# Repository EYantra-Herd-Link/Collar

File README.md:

# HerdLink Collar V1

HerdLink Collar V1 is a smart edge-computing tracking and health monitoring collar designed for livestock. Built around the Seeed Studio XIAO ESP32-C3, the collar integrates motion sensing, temperature and humidity monitoring, and audio analysis to infer animal behaviors such as grazing, ruminating, walking, and resting. It transmits telemetry data wirelessly via UDP.

## Features

*   **Behavioral Inference:** Utilizes a 6-axis IMU (MPU6050) to calculate activity jerk and variance, categorizing behavior into states like Grazing, Ruminating, Walking, Resting, and High/Low Activity Alerts.
*   **Audio Edge Processing:** Captures audio via an I2S microphone and performs on-device Fast Fourier Transform (FFT) to extract Mel-frequency features and audio magnitude.
*   **Health & Environmental Monitoring:** Measures body temperature using a Dallas DS18B20 sensor and environmental temperature/humidity using an AHT20 sensor.
*   **Power Efficiency:** Implements FreeRTOS tasks, hardware interrupts, and sleep modes (ESP32 Light Sleep) to optimize battery life.
*   **Wireless Telemetry:** Broadcasts structured JSON telemetry payloads over WiFi via UDP for local network collection.

## Hardware Components

*   **Microcontroller:** Seeed Studio XIAO ESP32-C3
*   **Motion Sensor:** MPU6050 (Accelerometer & Gyroscope)
*   **Body Temperature Sensor:** Dallas DS18B20 (OneWire)
*   **Environment Sensor:** AHT20 (Temperature & Humidity)
*   **Microphone:** I2S Microphone
*   **Custom PCB:** KiCad designs included for the main logic board and power management board.

## Project Structure

*   `Board Firmware/Sender/`: C++ PlatformIO project containing the ESP32-C3 edge firmware.
*   `Board Firmware/Reciever/`: Python script to receive and decode UDP telemetry data.
*   `PCB_Design/HerdLinkV1/`: KiCad project and Gerber files for the main collar PCB.
*   `PCB_Design/HerdLinkV1 Power/PowerBoard/`: KiCad project for the power management board.

## Setup and Installation

### 1. Firmware (Sender)

The firmware is built using PlatformIO.

1.  Open the `Board Firmware/Sender` directory in VS Code with the PlatformIO extension installed.
2.  Before flashing, update the WiFi credentials in `src/main.cpp`:
    ```cpp
    const char* WIFI_SSID     = "Your_SSID";
    const char* WIFI_PASSWORD = "Your_PASSWORD";
    ```
3.  Connect the XIAO ESP32-C3 and click the PlatformIO "Upload" button to compile and flash the firmware.

### 2. Receiver (Python script)

The receiver is a lightweight Python script that listens for incoming UDP packets.

1.  Navigate to the receiver directory:
    ```bash
    cd "Board Firmware/Reciever"
    ```
2.  Run the script (requires Python 3):
    ```bash
    python CowPilled.py
    ```
    The script will bind to `0.0.0.0:4210` and print incoming JSON telemetry payloads to the console.

## Telemetry Data Format

The device transmits data in JSON format over UDP. Example payload structure:

```json
{
  "id": "MAC_ADDRESS",
  "seq": 123,
  "ts": 1645000,
  "bt": 38.5,
  "et": 24.2,
  "eh": 45.0,
  "ax": 0.05,
  "ay": 0.98,
  "az": 0.12,
  "gx": 1.50,
  "gy": -0.20,
  "gz": 0.10,
  "gy_var": 0.054,
  "jerk": 45.2,
  "mot_int": 0,
  "err": 0,
  "v": 0.00,
  "s": -65,
  "af": [12.4, 45.2, 5.1, 0.0, 0.0, 0.0, 0.0, 0.0]
}
```

*   `id`: Device MAC address
*   `seq`: Sequence number
*   `ts`: Device uptime timestamp (ms)
*   `bt`: Body temperature (Celsius)
*   `et`: Environmental temperature (Celsius)
*   `eh`: Environmental humidity (%)
*   `ax`, `ay`, `az`: Accelerometer data
*   `gx`, `gy`, `gz`: Gyroscope data
*   `gy_var`: Gyroscope Y-axis variance
*   `jerk`: Calculated activity jerk
*   `mot_int`: Motion interrupt flag (1 if triggered, 0 otherwise)
*   `err`: Error code (currently 0)
*   `v`: Voltage (placeholder)
*   `s`: WiFi RSSI signal strength
*   `af`: Array of Audio Features (Mel bins)

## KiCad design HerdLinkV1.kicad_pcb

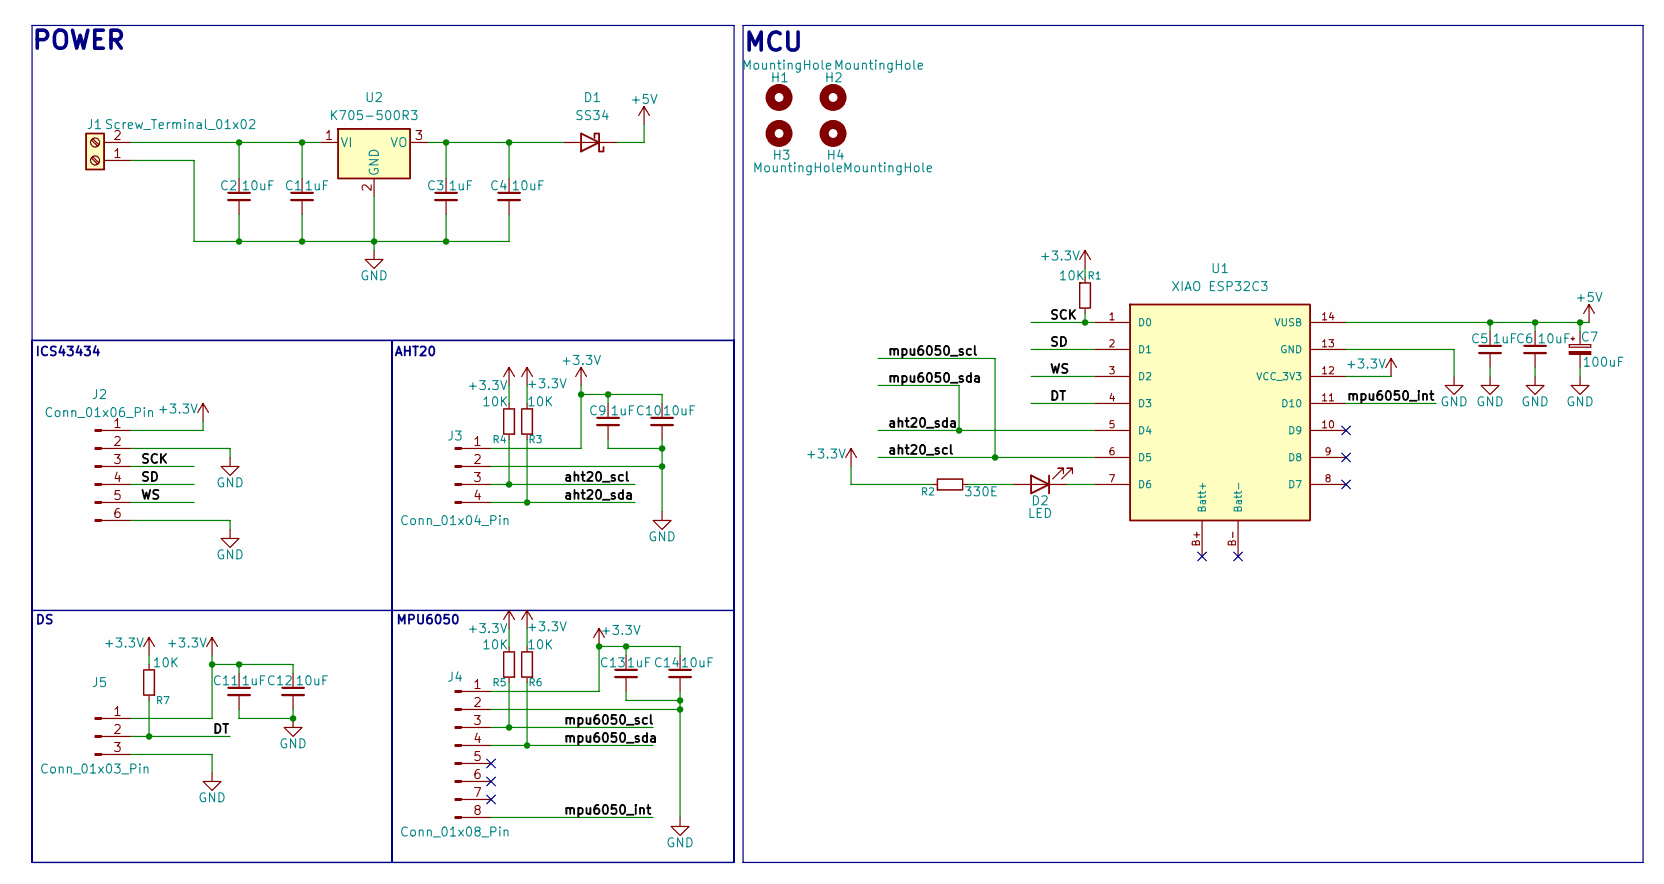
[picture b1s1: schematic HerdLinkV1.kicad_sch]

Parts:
C1, C3, C5, C9, C11, C13: 1uF; C_1206_3216Metric
C2, C4, C6, C10, C12, C14: 10uF; C_1206_3216Metric
C7: 100uF; CP_Radial_D4.0mm_P1.50mm
D1: SS34; D_SMA
D2: LED; LED_0603_1608Metric
H1, H2, H3, H4: MountingHole; MountingHole_3.2mm_M3
J1: Screw_Terminal_01x02; TerminalBlock_Xinya_XY308-2.54-2P_1x02_P2.54mm_Horizontal
J2: Conn_01x06_Pin; PinHeader_1x06_P2.54mm_Vertical
J3: Conn_01x04_Pin; PinHeader_1x04_P2.54mm_Vertical
J4: Conn_01x08_Pin; PinHeader_1x08_P2.54mm_Vertical
J5: Conn_01x03_Pin; PinHeader_1x03_P2.54mm_Vertical
R1, R3, R4, R5, R6, R7: 10K; R_1206_3216Metric_Pad1.30x1.75mm_HandSolder
R2: 330E; R_1206_3216Metric_Pad1.30x1.75mm_HandSolder
U1: XIAO ESP32C3; xiao_esp32c3
U2: K705-500R3; TO-220-3_Vertical

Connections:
+3.3V: C9.1, C10.1, C11.1, C12.1, C13.1, C14.1, J2.1, J3.1, J4.1, J5.1, R1.1, R2.1, R3.2, R4.2, R5.2, R6.2, R7.2, U1.12 (VCC_3V3)
+5V: C5.1, C6.1, C7.1, D1.1 (K), U1.14 (VUSB)
/DT: J5.2, R7.1, U1.4 (D3)
/SCK: J2.3, R1.2, U1.1 (D0)
/SD: J2.4, U1.2 (D1)
/WS: J2.5, U1.3 (D2)
/aht20_scl: J3.3, J4.3, R4.1, R5.1, U1.6 (D5)
/aht20_sda: J3.4, J4.4, R3.1, R6.1, U1.5 (D4)
/mpu6050_int: J4.8, U1.11 (D10)
GND: C1.2, C2.2, C3.2, C4.2, C5.2, C6.2, C7.2, C9.2, C10.2, C11.2, C12.2, C13.2, C14.2, J1.1, J2.2, J2.6, J3.2, J4.2, J5.3, U1.13 (GND), U2.2 (GND)
unnamed: C3.1, C4.1, D1.2 (A), U2.3 (VO)
unnamed: D2.2 (A), R2.2
unnamed: D2.1 (K), U1.7 (D6)
unnamed: C1.1, C2.1, J1.2, U2.1 (VI)

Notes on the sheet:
MCU
MPU6050
AHT20
ICS43434
POWER

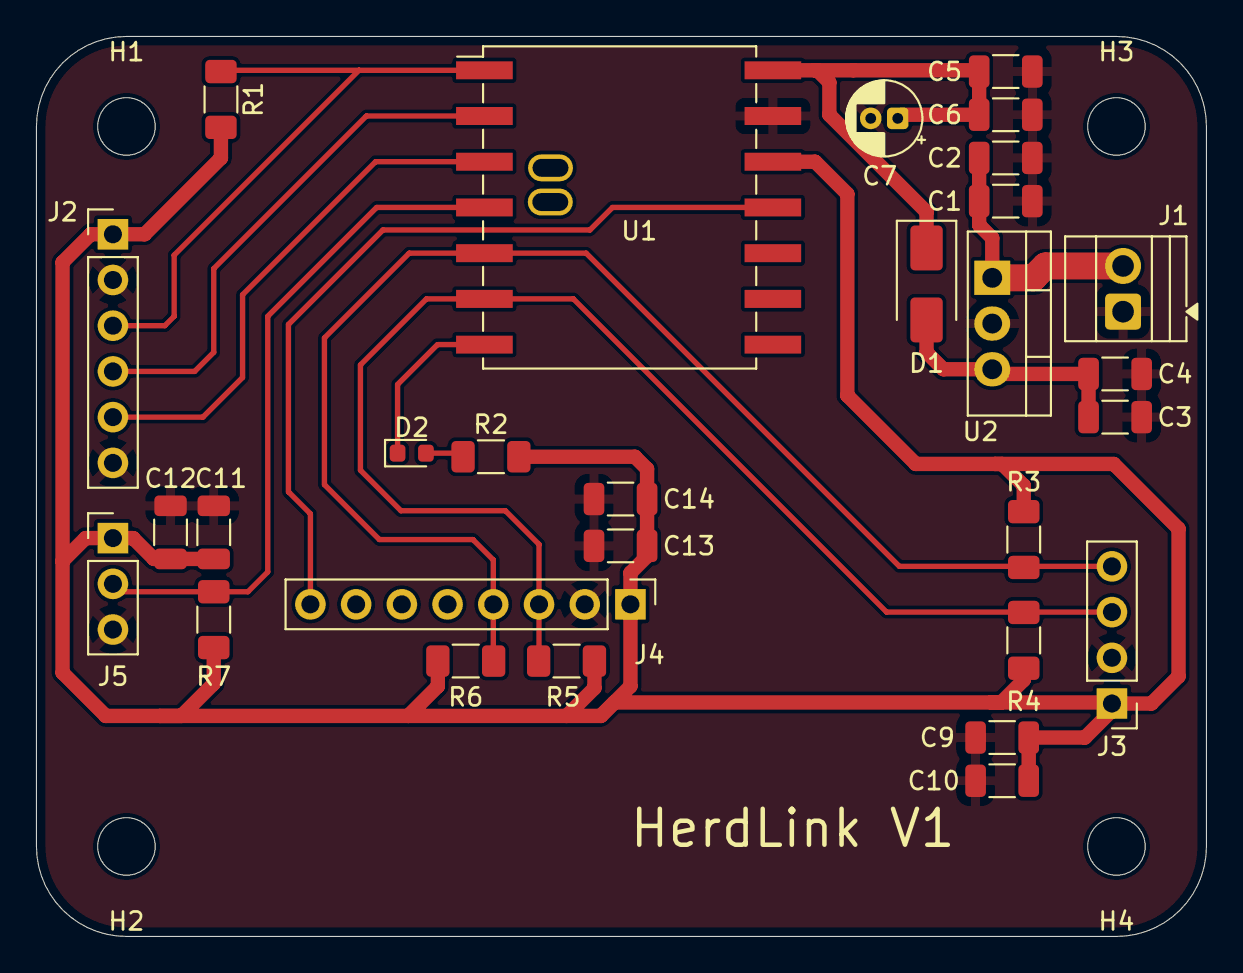
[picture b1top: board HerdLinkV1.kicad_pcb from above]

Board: 2 copper layers, 65.0 x 50.0 mm, 33 parts (0 on the bottom side), 14 nets.

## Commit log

2026-02-18 Added UDP reciever
2026-02-19 Added Collar Firmware
2026-02-19 Update README formatting and project description
2026-02-20 Updated Firmware, Memory safe and sends only raw data.
2026-02-22 Version 2.5 with no sleep functions
2026-02-22 Updated with Light Sleep
2026-02-22 Minor bug fixes with the watchdog timer.
2026-02-24 Added PCB files
2026-02-25 Updated firmware with working motion interrupts and RSSI updates
2026-02-26 Updated with Tuned Values.
2026-03-20 Final Version
2026-03-20 Updated Sender
